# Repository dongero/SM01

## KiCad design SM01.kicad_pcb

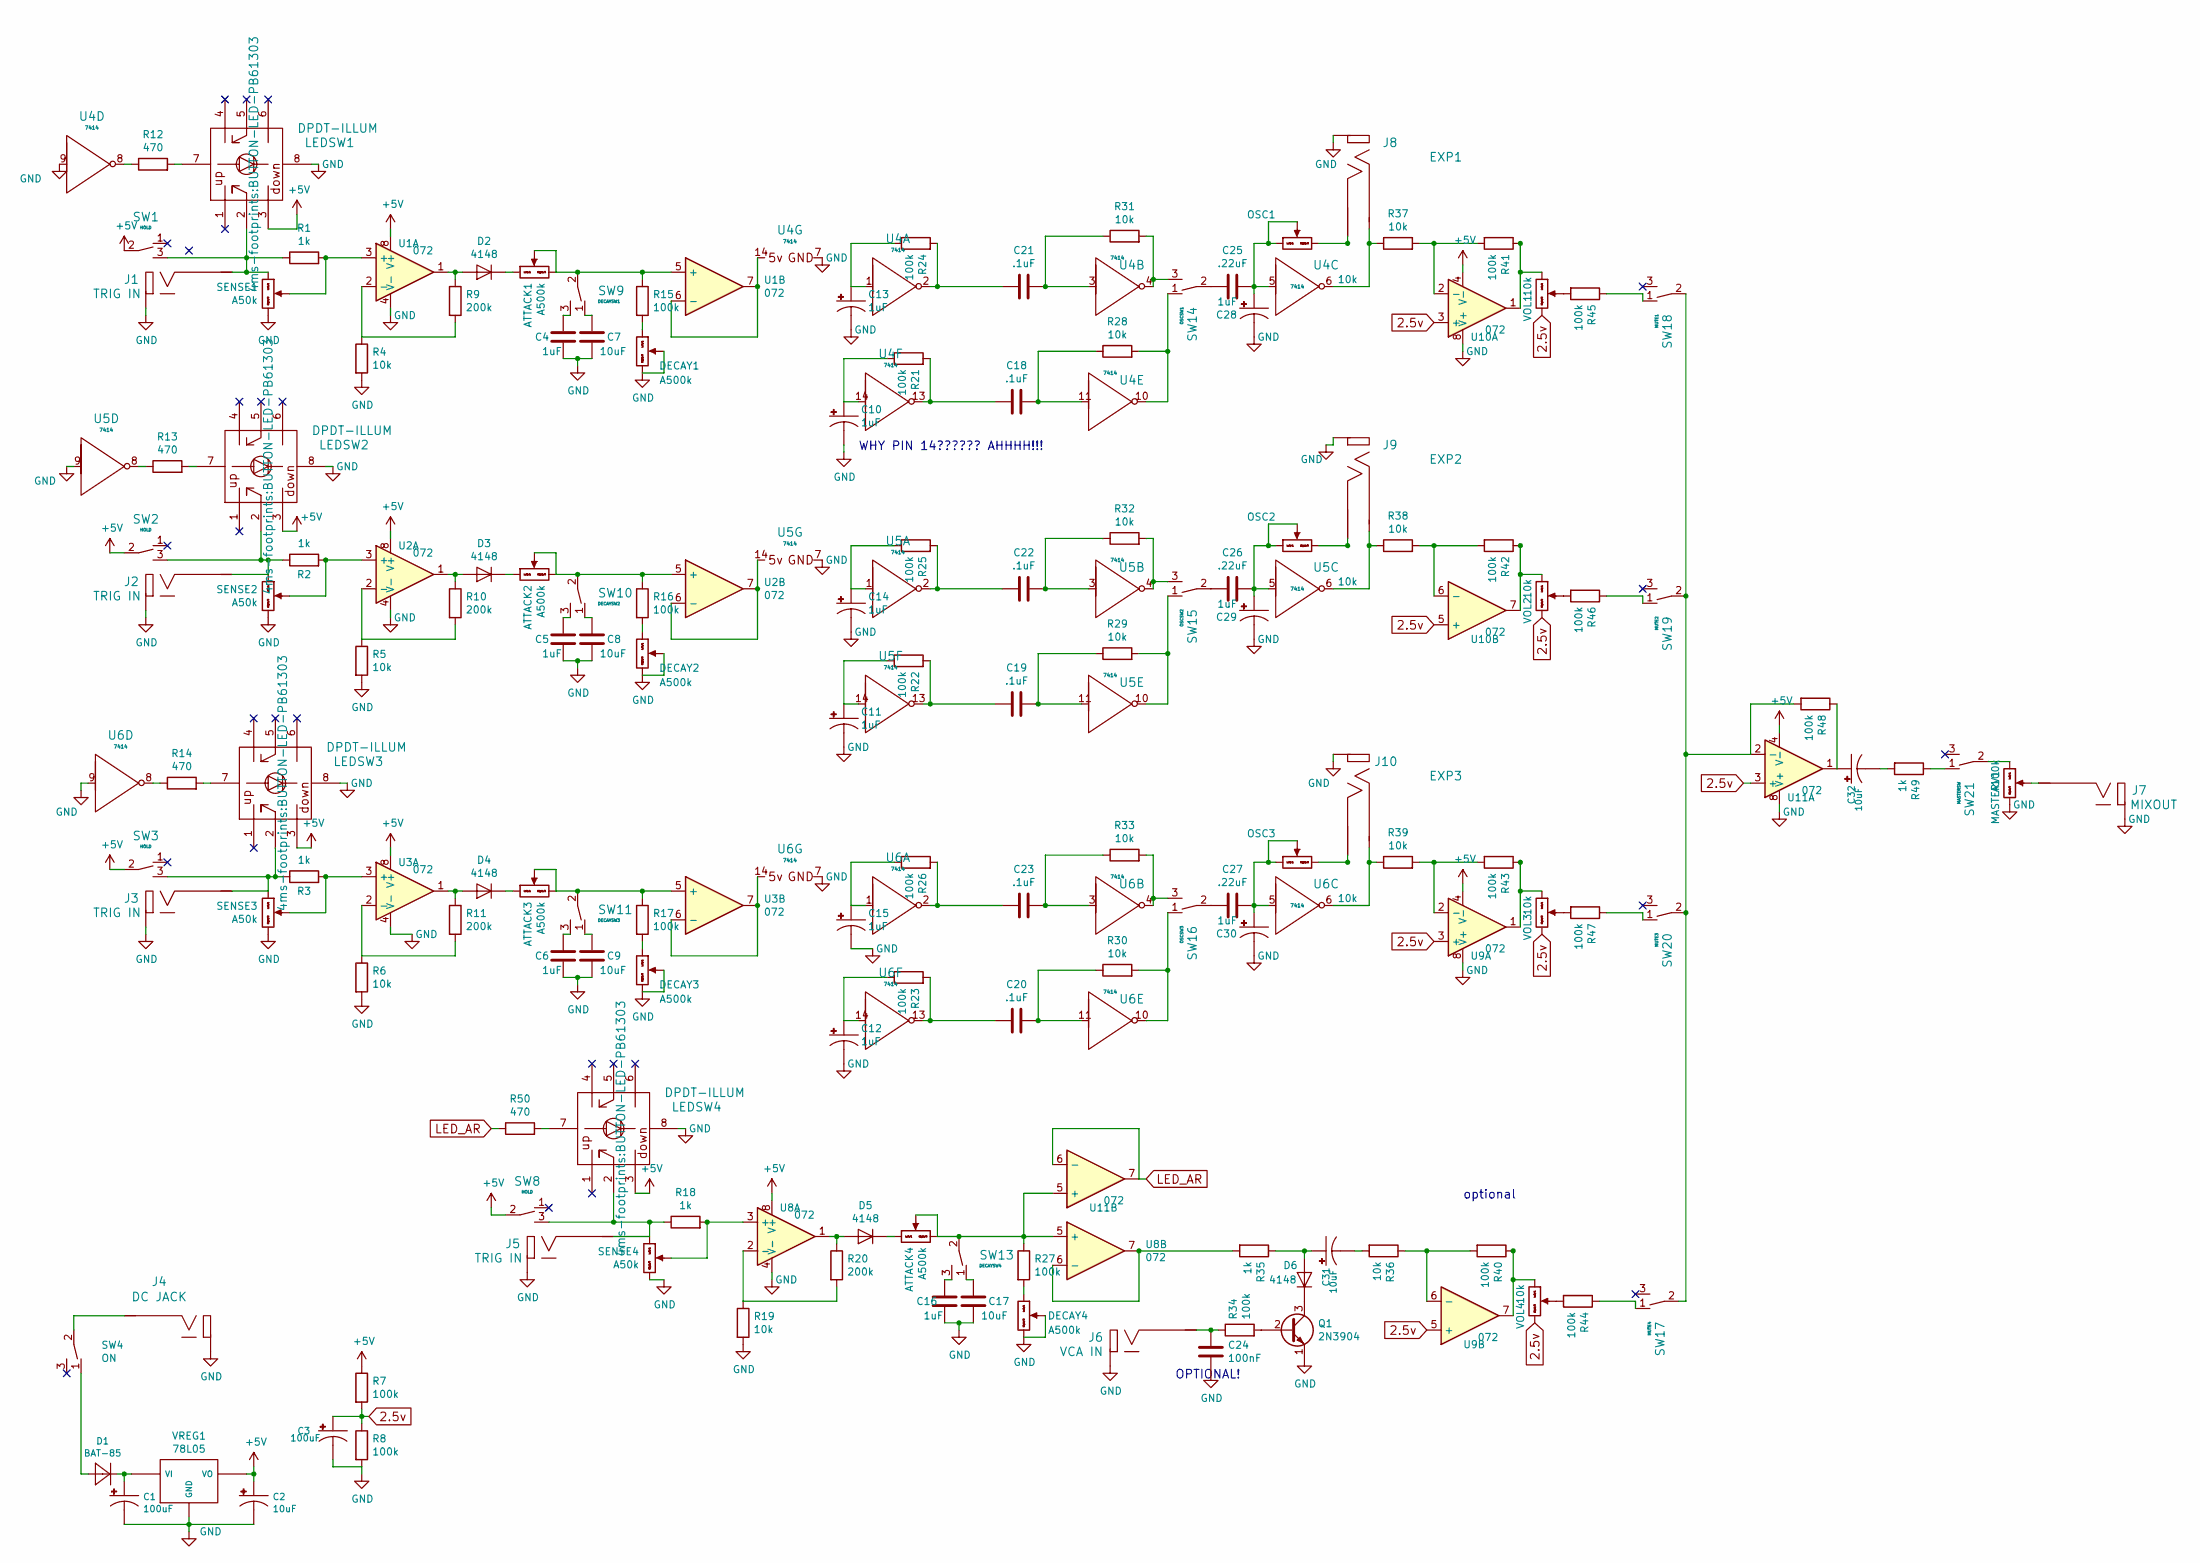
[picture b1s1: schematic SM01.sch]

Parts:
ATTACK1, ATTACK2, ATTACK3, ATTACK4: A500k; POT-9MM-ALPHA
C1, C3: 100uF; Cap_Electrolytic_TH
C2, C31, C32: 10uF; Cap_Electrolytic_TH
C4, C5, C6, C16: 1uF; Cap_Ceramic_TH
C7, C8, C9, C17: 10uF; Cap_Ceramic_TH
C10, C11, C12, C13, C14, C15, C28, C29, C30: 1uF; Cap_Electrolytic_TH
C18, C19, C20, C21, C22, C23: .1uF; Cap_Ceramic_TH
C24: 100nF; Cap_Ceramic_TH
C25, C26, C27: .22uF; Cap_Ceramic_TH
D1: BAT-85; Diode_BAT-85S_TH
D2, D3, D4, D5, D6: 4148; Diode_BAT-85S_TH
DECAY1, DECAY2, DECAY3, DECAY4: A500k; POT-9MM-ALPHA
J1, J2, J3, J5: TRIG IN; Jack_Instrument
J4: DC JACK; Jack_DC
J6: VCA IN; Jack_Instrument
J7: MIXOUT; Jack_Instrument
J8: EXP1; Jack_Instrument_exp
J9: EXP2; Jack_Instrument_exp
J10: EXP3; Jack_Instrument_exp
LEDSW1, LEDSW2, LEDSW3, LEDSW4: DPDT-ILLUM; BUTTON-LED-PB61303
MASTERV1: A100k; POT-9MM-ALPHA
OSC1, OSC2, OSC3: 10k; POT-9MM-ALPHA
Q1: 2N3904; TO-92_Molded_Narrow
R1, R2, R3, R18, R35, R49: 1k; Resistor_TH_300
R4, R5, R6, R19, R28, R29, R30, R31, R32, R33, R36, R37, R38, R39: 10k; Resistor_TH_300
R7, R8, R15, R16, R17, R21, R22, R23, R24, R25, R26, R27, R34, R40, R41, R42, R43, R44, R45, R46, R47, R48: 100k; Resistor_TH_300
R9, R10, R11, R20: 200k; Resistor_TH_300
R12, R13, R14, R50: 470; Resistor_TH_300
SENSE1, SENSE2, SENSE3, SENSE4: A50k; POT-9MM-ALPHA
SW1, SW2, SW3, SW8: HOLD; SPDT-SUB
SW4: ON; SPDT-SUB
SW9: DECAYSW1; SPDT-SUB
SW10: DECAYSW2; SPDT-SUB
SW11: DECAYSW3; SPDT-SUB
SW13: DECAYSW4; SPDT-SUB
SW14: OSCSW1; SPDT-SUB
SW15: OSCSW2; SPDT-SUB
SW16: OSCSW3; SPDT-SUB
SW17: MUTE4; SPDT-SUB
SW18: MUTE1; SPDT-SUB
SW19: MUTE2; SPDT-SUB
SW20: MUTE3; SPDT-SUB
SW21: MASTERSW; SPDT-SUB
U1, U2, U3, U8, U9, U10, U11: 072; DIP_8pin_TL072_TH
U4, U5, U6: 7414; DIP-14_W7.62mm
VOL1, VOL2, VOL3, VOL4: 10k; POT-9MM-ALPHA
VREG1: 78L05; Regulator_5V_7805_LARGE_TH

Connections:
2.5v: C3.1 (+), R7.2, R8.1, U9.3 (+), U9.5 (+), U10.3 (+), U10.5 (+), U11.3 (+), VOL1.3 (Right), VOL2.3 (Right), VOL3.3 (Right), VOL4.3 (Right)
+5V: C2.1 (+), LEDSW1.3 (DOWN-A), LEDSW2.3 (DOWN-A), LEDSW3.3 (DOWN-A), LEDSW4.3 (DOWN-A), R7.1, SW1.2, SW2.2, SW3.2, SW8.2, U1.8 (V+), U2.8 (V+), U3.8 (V+), U8.8 (V+), U9.4 (V-), U10.4 (V-), U11.4 (V-), VREG1.3 (VO)
GND: C1.2 (-), C2.2 (-), C3.2 (-), C4.1, C5.1, C6.1, C7.2, C8.2, C9.2, C10.2 (-), C11.2 (-), C12.2 (-), C13.2 (-), C14.2 (-), C15.2 (-), C16.1, C17.2, C24.2, C28.2 (-), C29.2 (-), C30.2 (-), DECAY1.2 (Center), DECAY1.3 (Right), DECAY2.2 (Center), DECAY2.3 (Right), DECAY3.2 (Center), DECAY3.3 (Right), DECAY4.2 (Center), DECAY4.3 (Right), J1.2 (GND), J2.2 (GND), J3.2 (GND), J4.2 (GND), J5.2 (GND), J6.2 (GND), J7.2 (GND), J8.3 (SHEILD), J9.3 (SHEILD), J10.3 (SHEILD), LEDSW1.8 (C), LEDSW2.8 (C), LEDSW3.8 (C), LEDSW4.8 (C), MASTERV1.3 (Right), Q1.1 (E), R4.2, R5.2, R6.2, R8.2, R19.2, SENSE1.3 (Right), SENSE2.3 (Right), SENSE3.3 (Right), SENSE4.3 (Right), U1.4 (V-), U2.4 (V-), U3.4 (V-), U4.7, U4.9, U5.7, U5.9, U6.7, U6.9, U8.4 (V-), U9.8 (V+), U10.8 (V+), U11.8 (V+), VREG1.2 (GND)
LED_AR: R50.1, U11.6 (-), U11.7
unnamed: ATTACK1.1 (Left), D2.1 (K)
unnamed: ATTACK1.2 (Center), ATTACK1.3 (Right), R15.1, SW9.2, U1.5 (+)
unnamed: ATTACK2.1 (Left), D3.1 (K)
unnamed: ATTACK2.2 (Center), ATTACK2.3 (Right), R16.1, SW10.2, U2.5 (+)
unnamed: ATTACK3.1 (Left), D4.1 (K)
unnamed: ATTACK3.2 (Center), ATTACK3.3 (Right), R17.1, SW11.2, U3.5 (+)
unnamed: ATTACK4.1 (Left), D5.1 (K)
unnamed: ATTACK4.2 (Center), ATTACK4.3 (Right), R27.1, SW13.2, U8.5 (+), U11.5 (+)
unnamed: C1.1 (+), D1.1 (C), VREG1.1 (VI)
unnamed: C4.2, SW9.3
unnamed: C5.2, SW10.3
unnamed: C6.2, SW11.3
unnamed: C7.1, SW9.1
unnamed: C8.1, SW10.1
unnamed: C9.1, SW11.1
unnamed: C13.1 (+), R24.1, U4.1
unnamed: C14.1 (+), R25.1, U5.1
unnamed: C15.1 (+), R26.1, U6.1
unnamed: C16.2, SW13.3
unnamed: C17.1, SW13.1
unnamed: C18.1, R28.1, U4.11
unnamed: C18.2, R21.2, U4.13
unnamed: C19.1, R29.1, U5.11
unnamed: C19.2, R22.2, U5.13
unnamed: C20.1, R30.1, U6.11
unnamed: C20.2, R23.2, U6.13
unnamed: C21.1, R31.1, U4.3
unnamed: C21.2, R24.2, U4.2
unnamed: C22.1, R32.1, U5.3
unnamed: C22.2, R25.2, U5.2
unnamed: C23.1, R33.1, U6.3
unnamed: C23.2, R26.2, U6.2
unnamed: C24.1, J6.1 (V), R34.1
unnamed: C25.1, C28.1 (+), OSC1.1 (Left), OSC1.2 (Center), U4.5
unnamed: C25.2, SW14.2
unnamed: C26.1, C29.1 (+), OSC2.1 (Left), OSC2.2 (Center), U5.5
unnamed: C26.2, SW15.2
unnamed: C27.1, C30.1 (+), OSC3.1 (Left), OSC3.2 (Center), U6.5
unnamed: C27.2, SW16.2
unnamed: C31.1 (+), D6.2 (A), R35.1
unnamed: C31.2 (-), R36.2
unnamed: C32.1 (+), R48.1, U11.1
unnamed: C32.2 (-), R49.2
unnamed: D1.2 (A), SW4.1
unnamed: D2.2 (A), R9.1, U1.1
unnamed: D3.2 (A), R10.1, U2.1
unnamed: D4.2 (A), R11.1, U3.1
unnamed: D5.2 (A), R20.1, U8.1
unnamed: D6.1 (K), Q1.3 (C)
unnamed: DECAY1.1 (Left), R15.2
unnamed: DECAY2.1 (Left), R16.2
unnamed: DECAY3.1 (Left), R17.2
unnamed: DECAY4.1 (Left), R27.2
unnamed: J1.1 (V), LEDSW1.2 (POLE-A), R1.1, SENSE1.1 (Left), SW1.3
unnamed: J2.1 (V), LEDSW2.2 (POLE-A), R2.1, SENSE2.1 (Left), SW2.3
unnamed: J3.1 (V), LEDSW3.2 (POLE-A), R3.1, SENSE3.1 (Left), SW3.3
unnamed: J4.1 (V), SW4.2
unnamed: J5.1 (V), LEDSW4.2 (POLE-A), R18.1, SENSE4.1 (Left), SW8.3
unnamed: J7.1 (V), MASTERV1.2 (Center)
unnamed: J8.1 (SW), OSC1.3 (Right)
unnamed: J8.2 (SIG), R37.1, U4.6
unnamed: J9.1 (SW), OSC2.3 (Right)
unnamed: J9.2 (SIG), R38.1, U5.6
unnamed: J10.1 (SW), OSC3.3 (Right)
unnamed: J10.2 (SIG), R39.1, U6.6
unnamed: LEDSW1.7 (A), R12.2
unnamed: LEDSW2.7 (A), R13.2
unnamed: LEDSW3.7 (A), R14.2
unnamed: LEDSW4.7 (A), R50.2
unnamed: MASTERV1.1 (Left), SW21.2
unnamed: Q1.2 (B), R34.2
unnamed: R1.2, SENSE1.2 (Center), U1.3 (+)
unnamed: R2.2, SENSE2.2 (Center), U2.3 (+)
unnamed: R3.2, SENSE3.2 (Center), U3.3 (+)
unnamed: R4.1, R9.2, U1.2 (-)
unnamed: R5.1, R10.2, U2.2 (-)
unnamed: R6.1, R11.2, U3.2 (-)
unnamed: R12.1, U4.8
unnamed: R13.1, U5.8
unnamed: R14.1, U6.8
unnamed: R18.2, SENSE4.2 (Center), U8.3 (+)
unnamed: R19.1, R20.2, U8.2 (-)
unnamed: R28.2, SW14.1, U4.10
unnamed: R29.2, SW15.1, U5.10
unnamed: R30.2, SW16.1, U6.10
unnamed: R31.2, SW14.3, U4.4
unnamed: R32.2, SW15.3, U5.4
unnamed: R33.2, SW16.3, U6.4
unnamed: R35.2, U8.6 (-), U8.7
unnamed: R36.1, R40.2, U9.6 (-)
unnamed: R37.2, R41.2, U10.2 (-)
unnamed: R38.2, R42.2, U10.6 (-)
unnamed: R39.2, R43.2, U9.2 (-)
unnamed: R40.1, U9.7, VOL4.1 (Left)
unnamed: R41.1, U10.1, VOL1.1 (Left)
unnamed: R42.1, U10.7, VOL2.1 (Left)
unnamed: R43.1, U9.1, VOL3.1 (Left)
unnamed: R44.1, SW17.1
unnamed: R44.2, VOL4.2 (Center)
unnamed: R45.1, SW18.1
unnamed: R45.2, VOL1.2 (Center)
unnamed: R46.1, SW19.1
unnamed: R46.2, VOL2.2 (Center)
unnamed: R47.1, SW20.1
unnamed: R47.2, VOL3.2 (Center)
unnamed: R48.2, SW17.2, SW18.2, SW19.2, SW20.2, U11.2 (-)
unnamed: R49.1, SW21.1

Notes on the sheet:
OPTIONAL!
optional
WHY PIN 14?????? AHHHH!!!

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
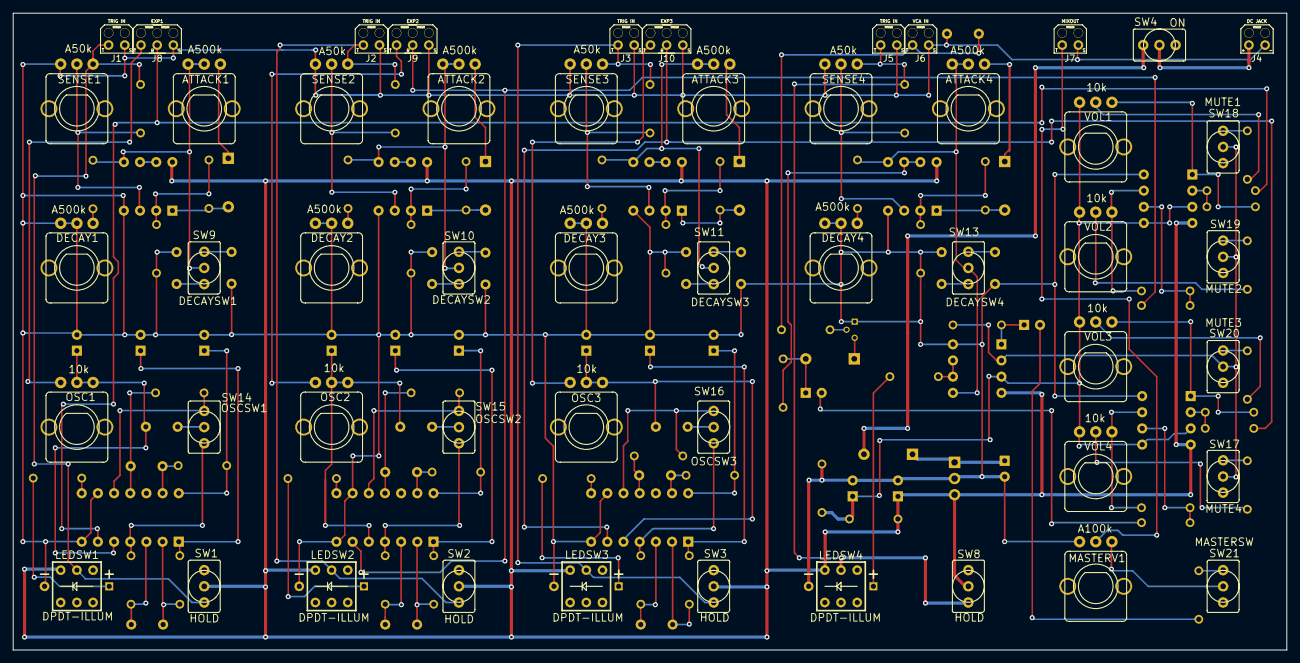
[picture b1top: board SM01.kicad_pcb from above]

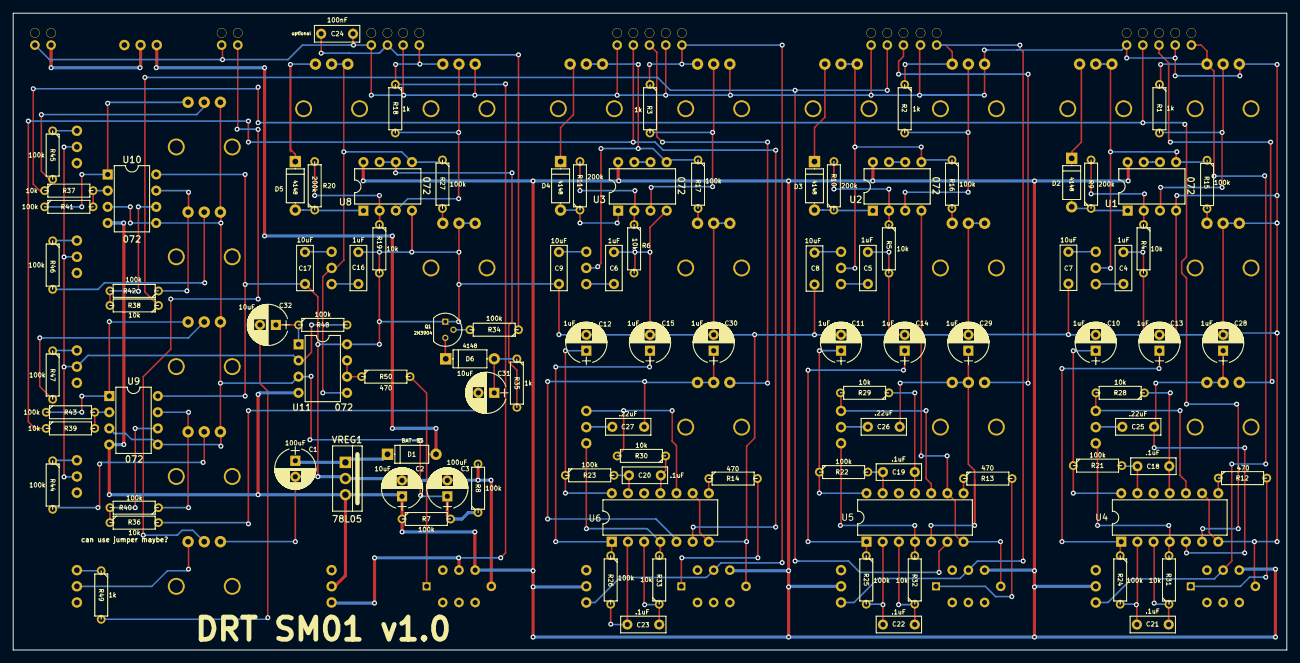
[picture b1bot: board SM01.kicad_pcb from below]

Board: 2 copper layers, 200.0 x 100.0 mm, 151 parts (100 on the bottom side), 117 nets.

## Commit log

2017-08-22 started sch
2017-08-26 basic layout complete
2017-09-01 finished one full channel and vca channel
2017-09-02 sorting PCB page
2017-09-02 organized channels
2017-09-03 continued laying out pcb - having issue with zfoot.pretty
2017-09-03 finished placing components - starting to connect traces
2017-09-03 finished channel 1 but theres so much more bullshit left
2017-09-03 finished laying traces and organizing ref
2017-09-04 fixed 2.5v tag issue
2017-09-05 added gbr - sent file in -HOPE IT WORKS!
2017-09-15 may have made changes
